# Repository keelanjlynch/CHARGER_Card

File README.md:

# CHARGER Card

## A compact, interactable business card created for The Univeristy of Alabama in Huntsville Electrical and Computer Engineering Department.

This project was created by Aadam Saafi, Austin Nash, John D'Alessandro, and Keelan Lynch. It utilizes a TFT LCD display, capacative touch buttons, USB interface for flashing/power, and an ESP32-S3-WROOM1.
The code for the project was written in Arduino IDE and the PCB design/layout was created using KiCad. Some of the features of the board in its current state include:

* Three educational activities relating to ECE disciplines included below:
* A Cyber Security activity of brute force byte decryption (similar to mastermind or wordle)
* An Electrical Engineering connect-the-dots activity where user connect electrical components to create an electrical connection
* A Computer Engineering activity where user adjusts inputs and logic gates to get the desired output
* Capacative touch calibration
* Menu selection
* Bitmap rendering

Some additions that could be made using the capabilities of the ESP32-S3:
* Bluetooth utilization
* Wi-Fi utilization
* Artifical Intelligence
* Additional games
* Resume display
* Web browser
* Animated display
* Etc.

## Demo Videos

https://www.youtube.com/watch?v=7o9A-FuoEWo

## How to install this project

1. Clone this project
2. Install Arduino IDE - https://www.arduino.cc/en/software/
3. Install KiCad - https://www.kicad.org/download/

## Opening this project in KiCad (we recommend using V2 of the design)

1. Open Buisness_Card_PCB.kicad_pro in KiCad

## Opening this project in Ardunio

1. Open ChargerCardSoftware.ino in Arduino IDE
2. In Board Manager, install esp32 by Espressif Systems
3. In Library Manager, install "Adafruit GFX Library" and "Adafruit ST7735 and ST7789 Library"
4. Ensure that the CHARGER Card is plugged into your computer via USB
5. From the top menu: Tools > Board: > esp32 > ESP32S3 Dev Module
6. Select the port that the board is currently connected to
7. Once set up, you can upload any changes made in code
8. If this is your first time connecting the board: Hold down the boot switch (lower push button), press and release the reset switch (upper push button), release boot switch. This will put the board into boot mode.

# Altering the code

It will be easiest if you edit this code within an installed verion of the Arduino IDE. The ChargerCardSoftware.ino file is where all code for the project currently resides. 
The bitmaps.h file has all the bitmaps used by the primary ino file. The code is seperate into the following sections: framework drawing functions, cyber activity, ee activity, cpe activity, and framework functions. Global variables can be found at the top of each section (i.e globals used by the cyber activity are found at the top of the cyber activity section).

The setup() and loop() functions are the core of any Arduino code and are located at the very bottom of ChargerCardSoftware.ino. Additional functions and their descriptions are listed below:

* calibrateTouch() - called in setup, establishes a baseline for the capacative touch inputs
* updateTouchReadings() - called in loop to get a current reading from the touch inputs
* touchTest(int i) - compares the given touch point i with the established baseline
* displayLogo() - called to display full sized UAH logo
* drawGithub() - displays bitmap of QR code to this github
* drawFaculty(int f) - called to display image and description for the given UAH ECE faculty member f
* drawMenuSelect() - draws/updates the left side of main menu when the cursor is moved
* drawBonusMenuSelect() - draws/updates the left side of bonus menu when the cursor is moved
* drawMainMenu() - draws main menu
* drawBonusMenu() - draws bonus menu
* drawAboutPage() - draws about page
* returnMainMenu() - used to make main menu our current scene
* moveSelectionLeft() and moveSelectionRight() - used by the CS and EE activity to update the cursor left or right
* toggleSelectedBit() - used by CS activity to toggle the bit highlighted by the cursor
* submitGuess() - used by CS activity when the user presses A
* drawUI() - used by CS activity to draw graphical user interface
* drawTopBar() - component of the CS activity gui
* drawCurrentGuess() - component of the CS activity gui
* drawPreviousGuesses() - component of the CS activity gui
* drawHintBar() - component of the CS activity gui
* drawStats() - component of the CS activity gui
* drawKeyboard() - component of the CS activity gui
* uint8_t countCorrectBits(uint8_t guess, uint8_t target) - CS activity function for counting how many bits are correct
* showVictory() - CS activity function to draw victory message
* showDefeat() - CS activity function to draw game over message
* String getBinaryString(uint8_t num) - string conversion in CS activity
* String getHexString(uint8_t num) - string conversion in CS activity
* newCyberGame() - called when CS activity begins or is reset
* selectCurrentNode() - EE activity function called when user presses A
* initLevel(int level) - EE activity function for level initialization
* setupLevelX() - X is a number, EE activity functions used to initialize each level
* handleNodeTouch(int nodeId) - EE activity function that handles logic for touch on current node
* checkCircuitComplete() - EE activity function that checks if circuit is complete
* drawConnection(int node1, int node2, uint16_t color, int offset) - EE activity function to draw wire connections
* drawComponentSymbol(int x, int y, ComponentType type, bool active) - EE activity function for drawing components
* drawCircuit() - top level EE activity function called when drawing the circuit
* drawNodeLabel(int nodeIndex, uint16_t textColor) - EE activity function that draws a label for each component
* drawControls() - EE activity GUI showing controls
* showError(const char* message) - EE activity error message
* showSuccess() - EE activity level win message
* showGameComplete() - congratulations message shown at the end of EE activity
* resetLevel() - EE activity function to reset current level
* checkVal(int i) - CPE activity recursive function used to test logical output from edited diagram
* drawCursor() - CPE activity function used to draw updated cursor position
* drawWire(int x0, int y0, int i) - CPE activity function to draw wire between current node pos (x0, y0) and other node i
* drawLogic(int i) - CPE activity function to draw/update an input component
* drawNot(int i) - CPE activity function to draw NOT gate
* drawAnd(int i) - CPE activity function to draw AND gate
* drawOr(int i) - CPE activity function to draw OR gate
* drawSwitch(int i) - CPE activity function to draw/update a switch
* drawLED(int i) - CPE activity function to draw output component
* drawComponent(int i) - top level CPE activity function for drawing logic components
* drawWin() - CPE activity function to draw level complete message
* drawCPELevel() - CPE activity function to draw current level
* componentInteract(int i) - CPE activity function that handles if user presses A on component
* startCPELevel(int l) - initializes current CPE level l
* updateCPE() - CPE activity function to refresh screen when an edit was made
* startCPE() - called to begin the CPE activity
* cpeInputHandling(int t) - CPE activity function to handle all acceptable touch button inputs
* enterScene(int s) - used in main menu to switch scene and initialize new scene
* enterBonusScene(int s) - used in main menu to enter bonus menu
* update_mm(int d) - update main menu
* update_bm(int d) - update bonus menu
* update_faculty(int f) - update faculty page
* update_about(int a) - update about page

## Adding Custom Bitmaps

Custom bitmaps can be created from any image and drawn very easily using the Adafruit GFX library. The steps for converting and displaying the image of your choice will be listed below:

1. download your desired image (.png or .jpeg would be best)
2. go to https://javl.github.io/image2cpp/
3. select your file
4. alter canvas size (max size is 320x170 for this device)
5. scale to fit or scale to fill
6. adjust brightness/alpha threshold to get your desired image
7. ensure that code output format is set to Arduino Code, single bitmap
8. change the name of the array to something simple
9. copy and paste array into bitmaps.h file
10. tft.drawBitmap([x_pos],[y_pos],[array name],[width],[height],[color])

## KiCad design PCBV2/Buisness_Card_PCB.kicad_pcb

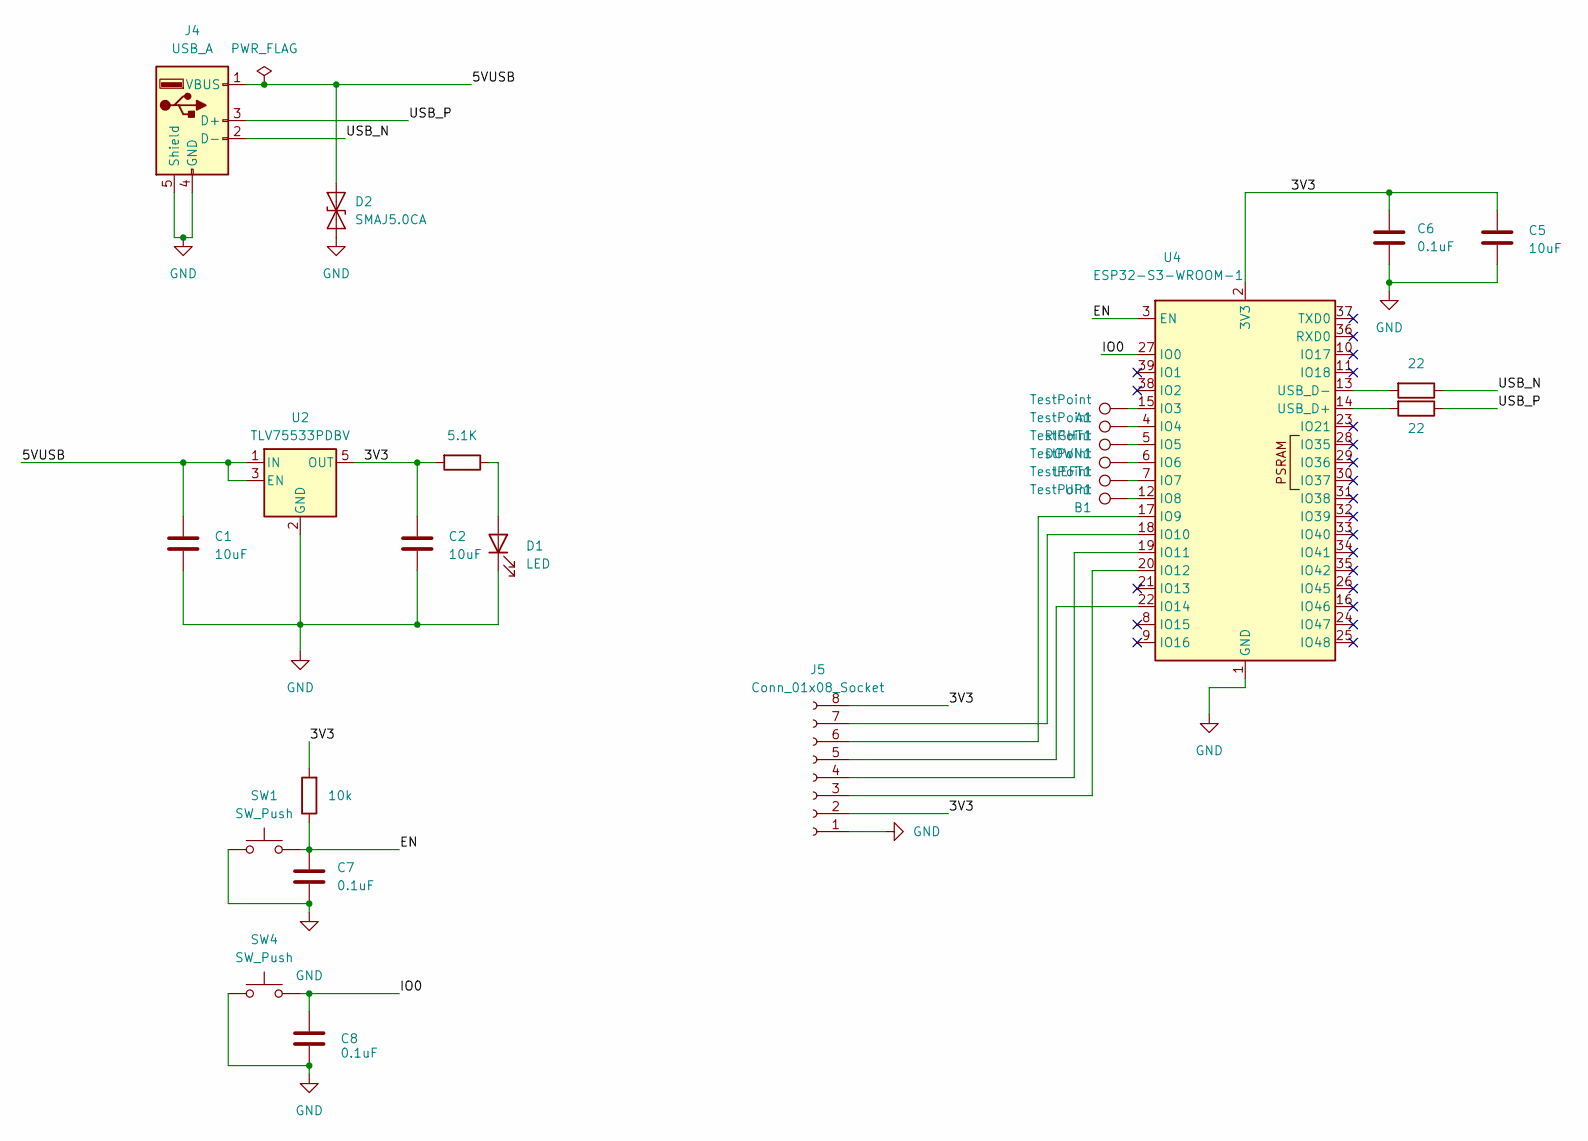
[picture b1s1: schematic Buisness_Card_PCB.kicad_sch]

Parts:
A1: TestPoint; TouchPad_8mm
B1: TestPoint; TouchPad_8mm
C1, C2, C5: 10uF; C_0201_0603Metric
C6, C7, C8: 0.1uF; C_0201_0603Metric
D1: LED; LED_0201_0603Metric
D2: SMAJ5.0CA; D_SMA
DOWN1: TestPoint; TouchPad_8mm
J4: USB_A; USB_A_PCB_Edge_receptacle
J5: Conn_01x08_Socket; PinHeader_1x08_P2.54mm_Vertical
LEFT1: TestPoint; TouchPad_8mm
R3: 5.1K; R_0201_0603Metric
R4, R6: 22; R_0201_0603Metric
R5: 10k; R_0201_0603Metric
RIGHT1: TestPoint; TouchPad_8mm
SW1, SW4: SW_Push; SW_SPST_TL3305A
U2: TLV75533PDBV; SOT-23-5
U4: ESP32-S3-WROOM-1
UP1: TestPoint; TouchPad_8mm

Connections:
/3V3: C2.2, C5.2, C6.2, J5.2, J5.8, R3.2, R5.2, U2.5 (OUT), U4.2 (3V3)
/5VUSB: C1.2, D2.2 (A2), J4.1 (VBUS), U2.1 (IN), U2.3 (EN)
/EN: C7.2, R5.1, SW1.2, U4.3 (EN)
/IO0: C8.2, SW4.2, U4.27 (IO0)
/USB_N: J4.2 (D-), R4.1
/USB_P: J4.3 (D+), R6.1
GND: C1.1, C2.1, C5.1, C6.1, C7.1, C8.1, D1.1 (K), D2.1 (A1), J4.4 (GND), J4.5 (Shield), J5.1, SW1.1, SW4.1, U2.2 (GND), U4.1 (GND), U4.40 (GND), U4.41 (GND)
unnamed: D1.2 (A), R3.1
unnamed: J5.3, U4.20 (IO12)
unnamed: J5.4, U4.19 (IO11)
unnamed: J5.5, U4.22 (IO14)
unnamed: J5.6, U4.17 (IO9)
unnamed: J5.7, U4.18 (IO10)
unnamed: A1.1, U4.15 (IO3)
unnamed: RIGHT1.1, U4.4 (IO4)
unnamed: DOWN1.1, U4.5 (IO5)
unnamed: LEFT1.1, U4.6 (IO6)
unnamed: U4.7 (IO7), UP1.1
unnamed: B1.1, U4.12 (IO8)
unnamed: R6.2, U4.14 (USB_D+)
unnamed: R4.2, U4.13 (USB_D-)

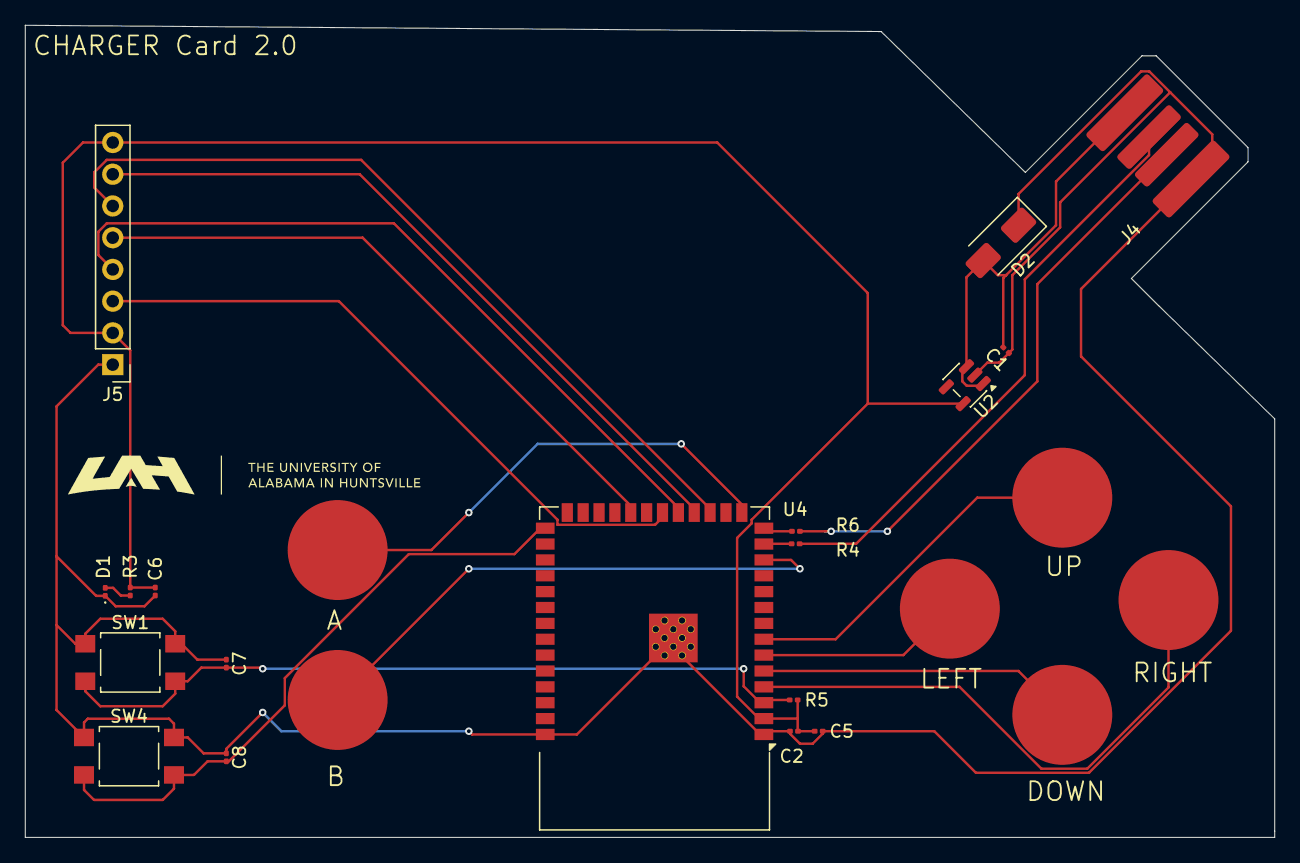
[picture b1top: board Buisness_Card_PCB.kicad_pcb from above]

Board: 2 copper layers, 100.0 x 65.0 mm, 24 parts (0 on the bottom side), 21 nets.

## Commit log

2026-04-24 Established new GitHub
2026-04-24 Added Github QR Code
2026-05-01 Create README.md
    initial README created
2026-05-01 Update README.md
    fixed video
2026-05-01 Update ChargerCardSoftware.ino
    removed copies of functions
2026-05-01 Update ChargerCardSoftware.ino
    undid changes made to ee activity
2026-05-01 created user manuals folder
2026-05-01 Additional User Manuals Added
